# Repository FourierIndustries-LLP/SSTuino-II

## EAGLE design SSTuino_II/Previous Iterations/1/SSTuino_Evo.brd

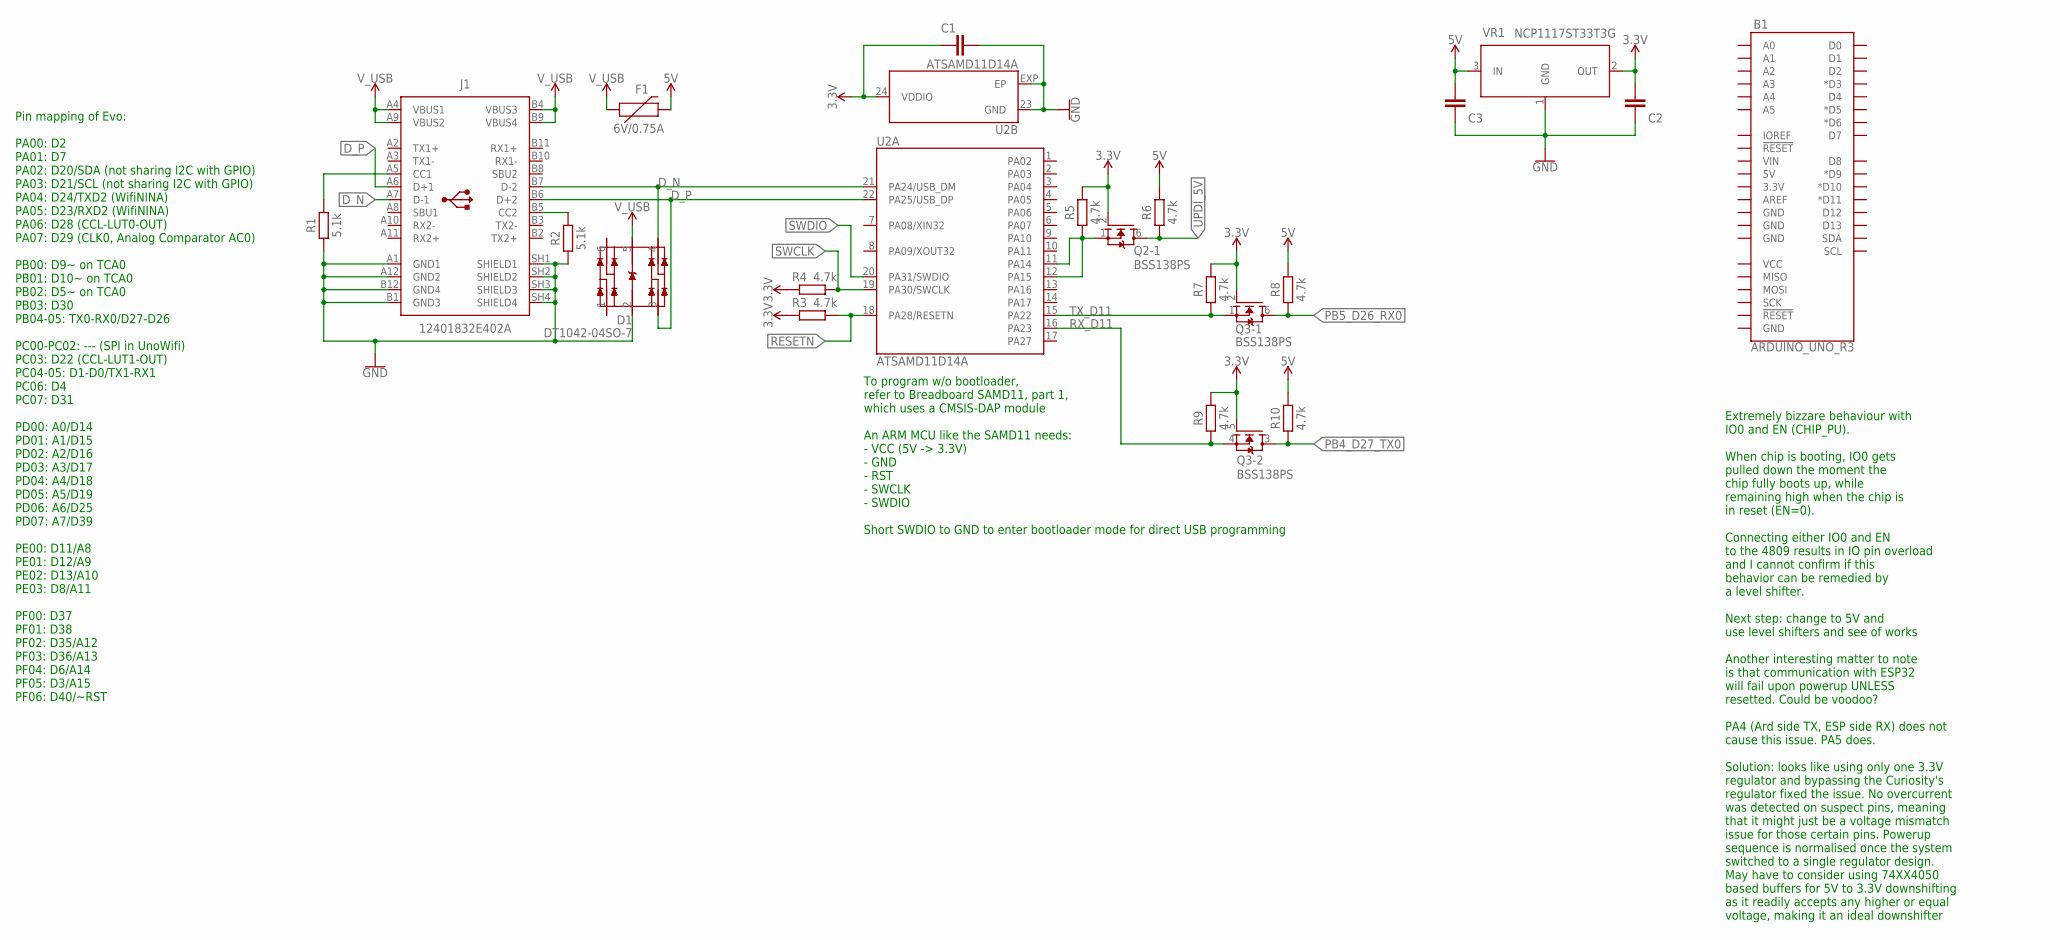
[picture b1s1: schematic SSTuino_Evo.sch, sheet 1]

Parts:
B1: ARDUINO_UNO_R3; ARDUINO_R3
C1: 100n; CAPC1005X60
C2, C3: 10uF; CAPC1608X85
D1: DT1042-04SO-7; SOT95P285X140-6N
F1: 6V/0.75A; 1206
J1: 12401832E402A
Q2, Q3: BSS138PS; ARDUINO-TRANSISTORS_SOT363
R1, R2: 5.1k; RESC1005X40
R3, R4, R5, R6, R7, R8, R9, R10: 4.7k; RESC1005X40
U2: ATSAMD11D14A; ARDUINO-UCS&SOCS_HVQFN24
VR1: NCP1117ST33T3G; SOT230P700X170-4

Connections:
3.3V: C1.1, C2.1, Q2.2 (G), Q3.2 (G), Q3.5 (G), R3.2, R4.2, R5.2, R7.2, R9.2, U2.24 (VDDIO), VR1.2 (OUT); also elsewhere on the board
5V: C3.1, F1.2, R6.2, R8.2, R10.2, VR1.3 (IN); also elsewhere on the board
CC1: J1.A5 (CC1), R1.2
CC2: J1.B5 (CC2), R2.2
D_N: D1.4 (IO3), J1.A7 (D-1), J1.B7 (D-2), U2.21 (PA24/USB_DM)
D_P: D1.3 (IO2), J1.A6 (D+1), J1.B6 (D+2), U2.22 (PA25/USB_DP)
GND: C1.2, C2.2, C3.2, D1.2 (VSS), J1.A1 (GND1), J1.A12 (GND2), J1.B1 (GND3), J1.B12 (GND4), J1.SH1 (SHIELD1), J1.SH2 (SHIELD2), J1.SH3 (SHIELD3), J1.SH4 (SHIELD4), R1.1, R2.1, U2.23 (GND), U2.EXP (EP), VR1.1 (GND); also elsewhere on the board
PB4_D27_TX0: Q3.3 (D), R10.1; also elsewhere on the board
PB5_D26_RX0: Q3.6 (D), R8.1; also elsewhere on the board
RESETN: R3.1, U2.18 (PA28/RESETN)
RX_D11: Q3.4 (S), R9.1, U2.16 (PA23)
SWCLK: R4.1, U2.19 (PA30/SWCLK)
SWDIO: U2.20 (PA31/SWDIO)
TX_D11: Q3.1 (S), R7.1, U2.15 (PA22)
UPDI_3V3: Q2.1 (S), R5.1, U2.11 (PA14), U2.12 (PA15)
UPDI_5V: Q2.6 (D), R6.1
V_USB: D1.5 (VCC), F1.1, J1.A4 (VBUS1), J1.A9 (VBUS2), J1.B4 (VBUS3), J1.B9 (VBUS4)

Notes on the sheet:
Pin mapping of Evo: PA00: D2 PA01: D7 PA02: D20/SDA (not sharing I2C with GPIO) PA03: D21/SCL (not sharing I2C with GPIO) PA04: D24/TXD2 (WifiNINA) PA05: D23/RXD2 (WifiNINA) PA06: D28 (CCL-LUT0-OUT) PA07: D29 (CLK0, Analog Comparator AC0) PB00: D9~ on TCA0 PB01: D10~ on TCA0 PB02: D5~ on TCA0 PB03: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
To program w/o bootloader, refer to Breadboard SAMD11, part 1, which uses a CMSIS-DAP module An ARM MCU like the SAMD11 needs: - VCC (5V -> 3.3V) - GND - RST - SWCLK - SWDIO Short SWDIO to GND to enter bootloader mode for direct USB programming
Extremely bizzare behaviour with IO0 and EN (CHIP_PU). When chip is booting, IO0 gets pulled down the moment the chip fully boots up, while remaining high when the chip is in reset (EN=0). Connecting either IO0 and EN to the 4809 results in IO pin overload and I cannot confirm if this behavior can 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

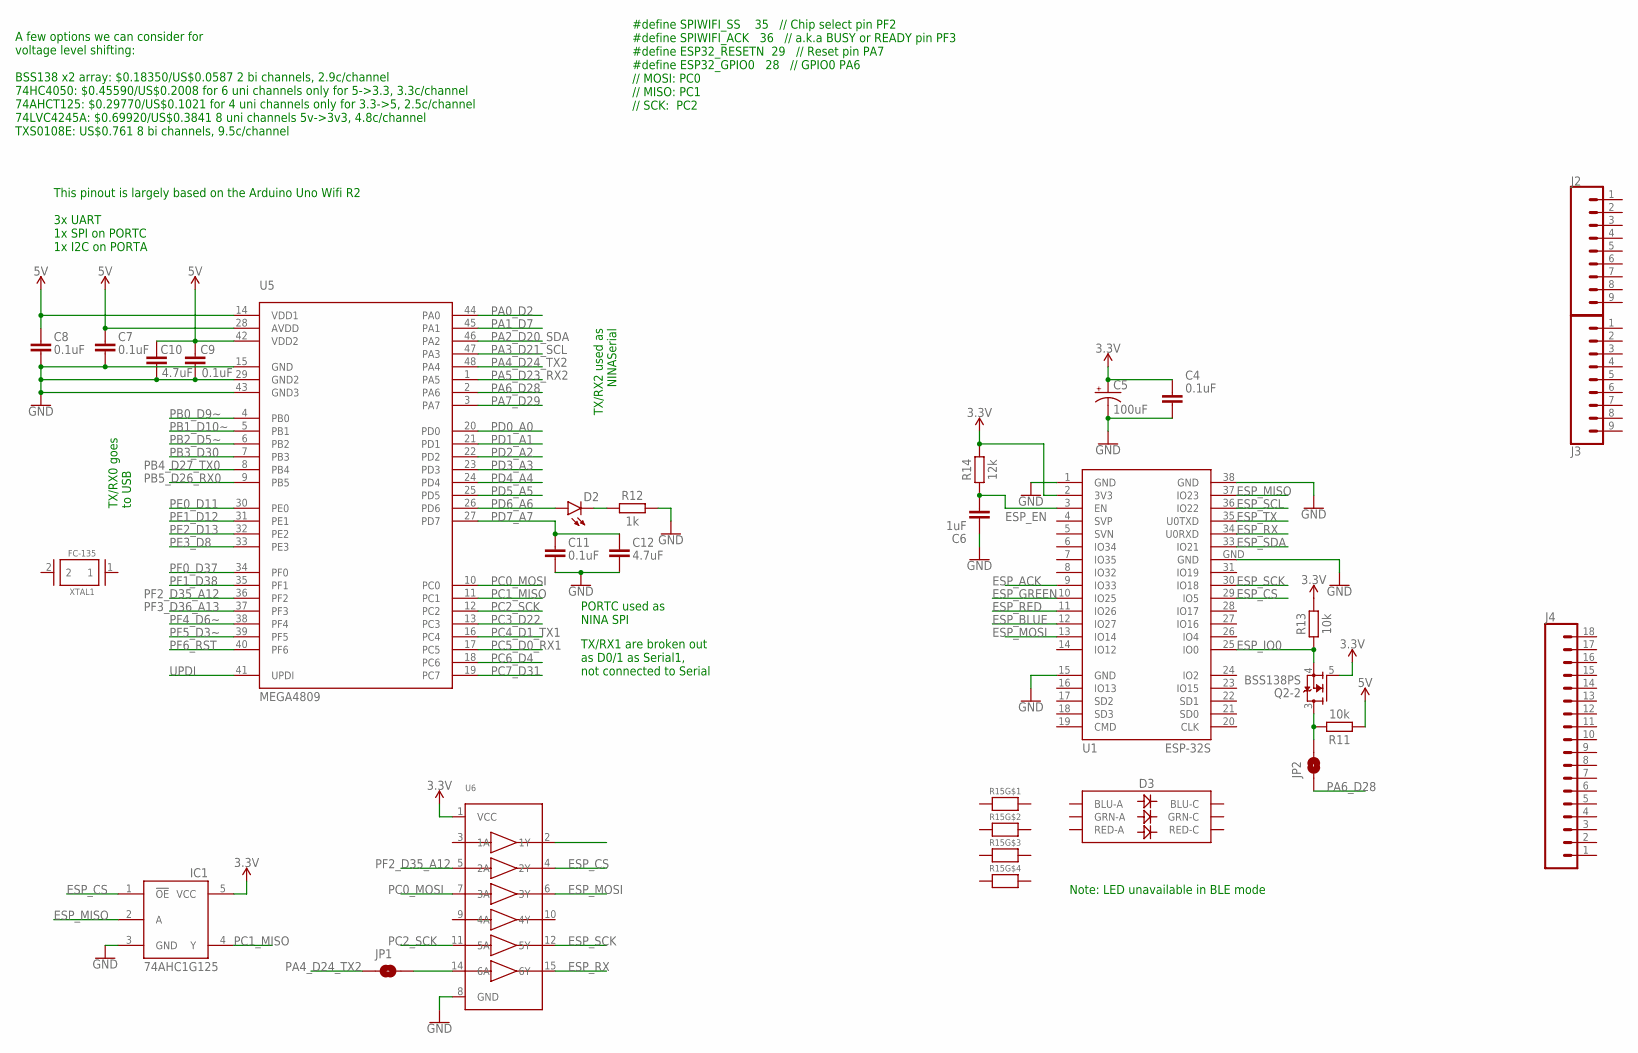
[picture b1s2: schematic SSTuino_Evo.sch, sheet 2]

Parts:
C4, C7, C8, C9, C11: 0.1uF; CAPC1005X60
C5: 100uF; CAPMP3216X180N
C6: 1uF; CAPC1005X60
C10, C12: 4.7uF; CAPC1005X60
D2: LED0603; LED-0603
D3: LED-RGBNO_IC; LED-TRICOLOR-5050
IC1: 74AHC1G125; SOT23-5L
J2, J3: CONN_09NO_SILK; 1X09_NO_SILK
J4: CONN_18; 1X18
JP1, JP2: JUMPER-SMT_2_NO_SILK; SMT-JUMPER_2_NO_SILK
Q2: BSS138PS; ARDUINO-TRANSISTORS_SOT363
R11, R13: 10k; RESC1005X40
R12: 1k; RESC1005X40
R14: 12k; RESC1005X40
R15: RESISTOR_4PACK; RESPACK_4X0603
U1: ESP-32S
U5: MEGA4809; TQFP48
U6: 74HC4050DTSSOP; TSSOP16
XTAL1: FC-135; XTAL330X1051X90N

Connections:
3.3V: C4.1, C5.1 (+), IC1.5 (VCC), Q2.5 (G), R13.2, R14.2, U1.2 (3V3), U6.1 (VCC); also elsewhere on the board
5V: C7.1, C8.1, C9.1, C10.1, R11.1, U5.14 (VDD1), U5.28 (AVDD), U5.42 (VDD2); also elsewhere on the board
ESP_ACK: U1.9 (IO33)
ESP_BLUE: U1.12 (IO27)
ESP_CS: IC1.1 (!OE), U1.29 (IO5), U6.4 (2Y)
ESP_EN: C6.2, R14.1, U1.3 (EN)
ESP_GREEN: U1.10 (IO25)
ESP_IO0: Q2.4 (S), R13.1, U1.25 (IO0)
ESP_MISO: IC1.2 (A), U1.37 (IO23)
ESP_MOSI: U1.13 (IO14), U6.6 (3Y)
ESP_RED: U1.11 (IO26)
ESP_RX: U1.34 (U0RXD), U6.15 (6Y)
ESP_SCK: U1.30 (IO18), U6.12 (5Y)
ESP_SCL: U1.36 (IO22)
ESP_SDA: U1.33 (IO21)
ESP_TX: U1.35 (U0TXD)
GND: C4.2, C5.2 (-), C6.1, C7.2, C8.2, C9.2, C10.2, C11.2, C12.2, IC1.3 (GND), R12.2, U1.1 (GND), U1.15 (GND), U1.38 (GND), U1.GND, U5.15 (GND), U5.29 (GND2), U5.43 (GND3), U6.8 (GND); also elsewhere on the board
unnamed: JP2.2, Q2.3 (D), R11.2
unnamed: D2.C, R12.1
unnamed: JP1.2, U6.14 (6A)
PA0_D2: U5.44 (PA0)
PA1_D7: U5.45 (PA1)
PA2_D20_SDA: U5.46 (PA2)
PA3_D21_SCL: U5.47 (PA3)
PA4_D24_TX2: JP1.1, U5.48 (PA4)
PA5_D23_RX2: U5.1 (PA5)
PA6_D28: JP2.1, U5.2 (PA6)
PA7_D29: U5.3 (PA7)
PB0_D9~: U5.4 (PB0)
PB1_D10~: U5.5 (PB1)
PB2_D5~: U5.6 (PB2)
PB3_D30: U5.7 (PB3)
PB4_D27_TX0: U5.8 (PB4); also elsewhere on the board
PB5_D26_RX0: U5.9 (PB5); also elsewhere on the board
PC0_MOSI: U5.10 (PC0), U6.7 (3A)
PC1_MISO: IC1.4 (Y), U5.11 (PC1)
PC2_SCK: U5.12 (PC2), U6.11 (5A)
PC3_D22: U5.13 (PC3)
PC4_D1_TX1: U5.16 (PC4)
PC5_D0_RX1: U5.17 (PC5)
PC6_D4: U5.18 (PC6)
PC7_D31: U5.19 (PC7)
PD0_A0: U5.20 (PD0)
PD1_A1: U5.21 (PD1)
PD2_A2: U5.22 (PD2)
PD3_A3: U5.23 (PD3)
PD4_A4: U5.24 (PD4)
PD5_A5: U5.25 (PD5)
PD6_A6: D2.A, U5.26 (PD6)
PD7_A7: C11.1, C12.1, U5.27 (PD7)
PE0_D11: U5.30 (PE0)
PE1_D12: U5.31 (PE1)
PE2_D13: U5.32 (PE2)
PE3_D8: U5.33 (PE3)
PF0_D37: U5.34 (PF0)
PF1_D38: U5.35 (PF1)
PF2_D35_A12: U5.36 (PF2), U6.5 (2A)
PF3_D36_A13: U5.37 (PF3)
PF4_D6~: U5.38 (PF4)
PF5_D3~: U5.39 (PF5)
PF6_RST: U5.40 (PF6)
UPDI: U5.41 (UPDI)

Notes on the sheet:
A few options we can consider for voltage level shifting: BSS138 x2 array: $0.18350/US$0.0587 2 bi channels, 2.9c/channel 74HC4050: $0.45590/US$0.2008 for 6 uni channels only for 5->3.3, 3.3c/channel 74AHCT125: $0.29770/US$0.1021 for 4 uni channels only for 3.3->5, 2.5c/channel 74LVC4245A: $0.69920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
This pinout is largely based on the Arduino Uno Wifi R2 3x UART 1x SPI on PORTC 1x I2C on PORTA
TX/RX2 used as NINASerial
PORTC used as NINA SPI
TX/RX1 are broken out as D0/1 as Serial1, not connected to Serial
TX/RX0 goes to USB
#define SPIWIFI_SS 35 // Chip select pin PF2 #define SPIWIFI_ACK 36 // a.k.a BUSY or READY pin PF3 #define ESP32_RESETN 29 // Reset pin PA7 #define ESP32_GPIO0 28 // GPIO0 PA6 // MOSI: PC0 // MISO: PC1 // SCK: PC2
Note: LED unavailable in BLE mode

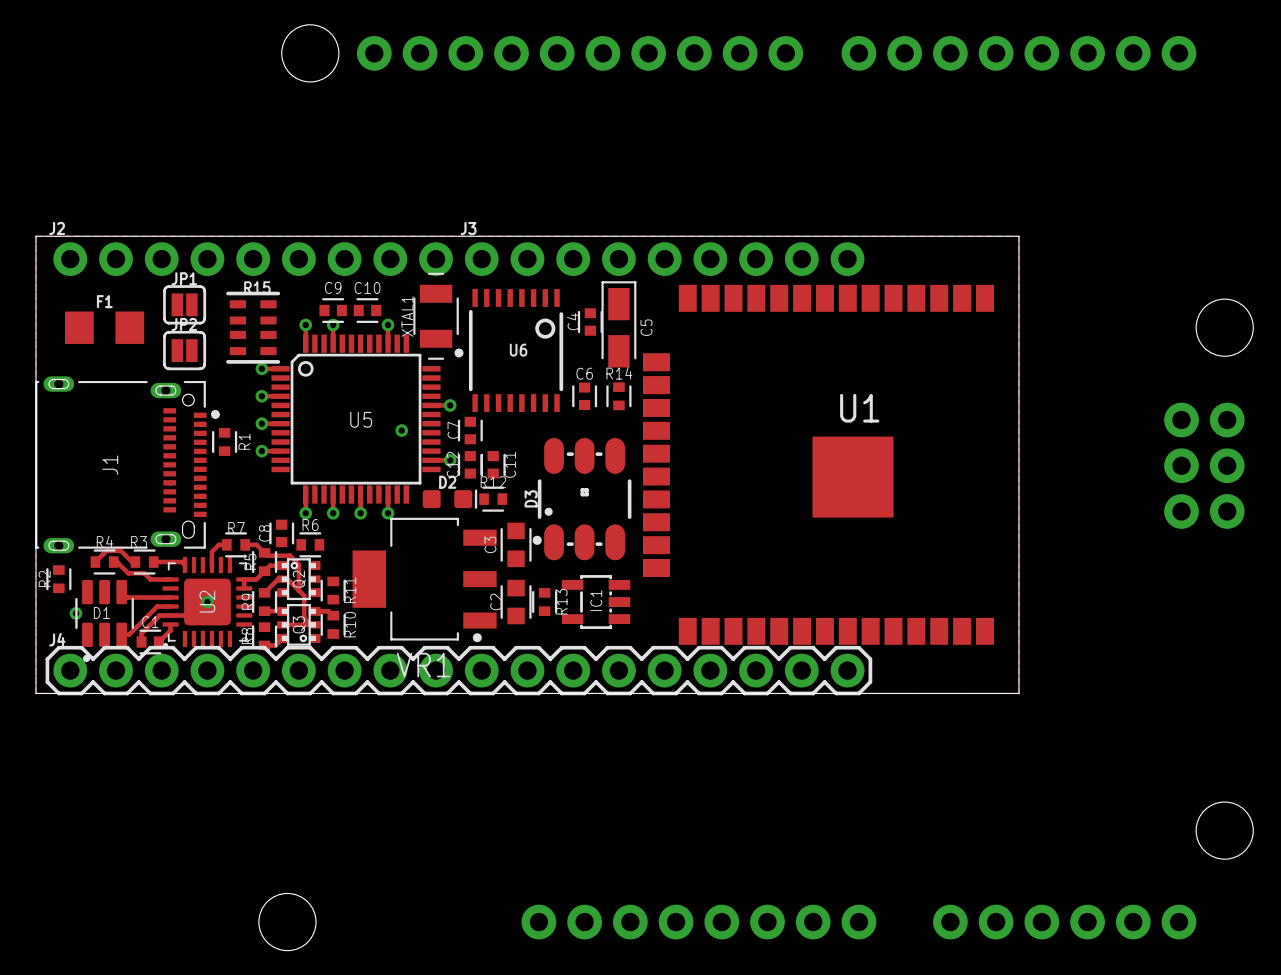
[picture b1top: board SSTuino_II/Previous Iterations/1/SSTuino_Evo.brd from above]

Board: 2 copper layers, 54.6 x 25.4 mm, 47 parts (0 on the bottom side), 34 nets.

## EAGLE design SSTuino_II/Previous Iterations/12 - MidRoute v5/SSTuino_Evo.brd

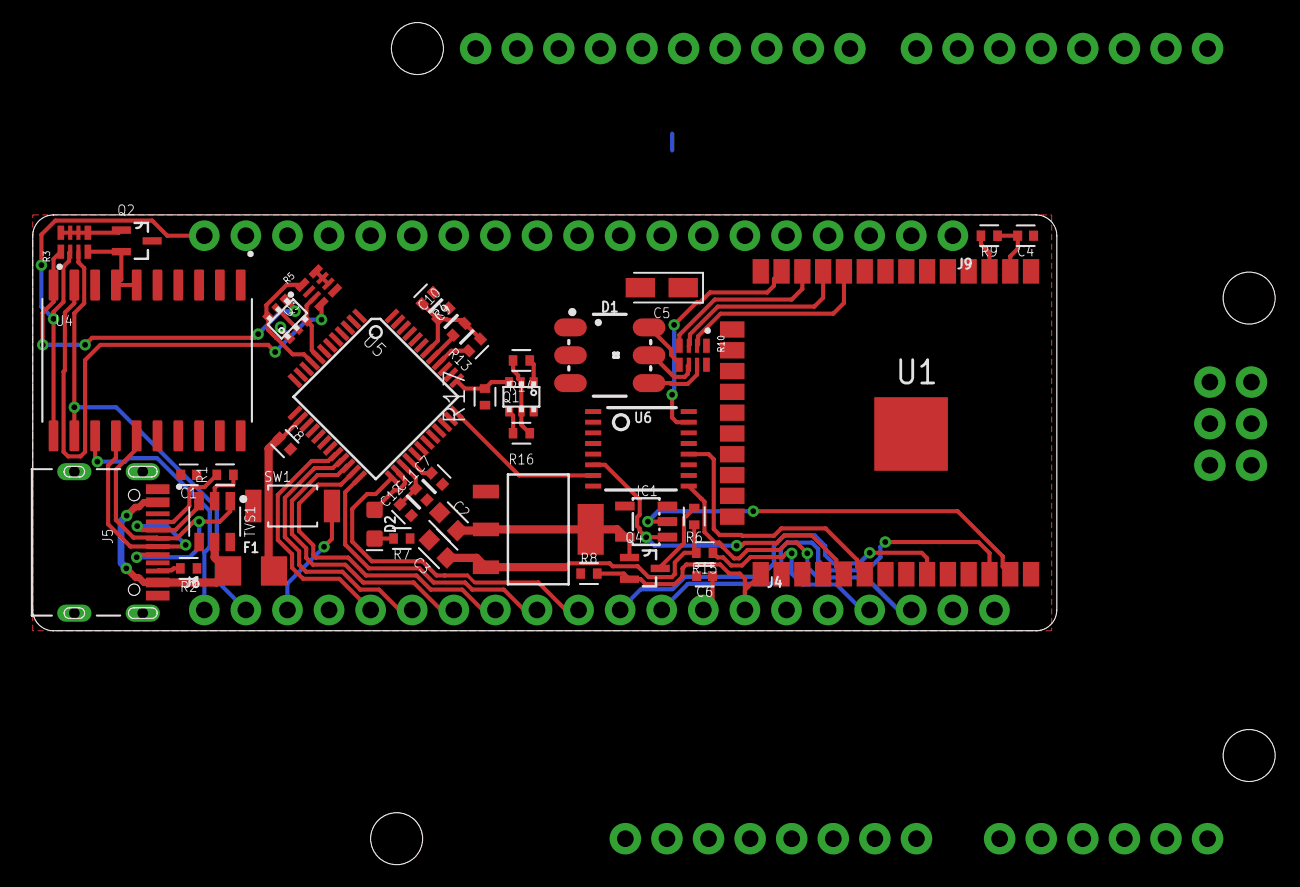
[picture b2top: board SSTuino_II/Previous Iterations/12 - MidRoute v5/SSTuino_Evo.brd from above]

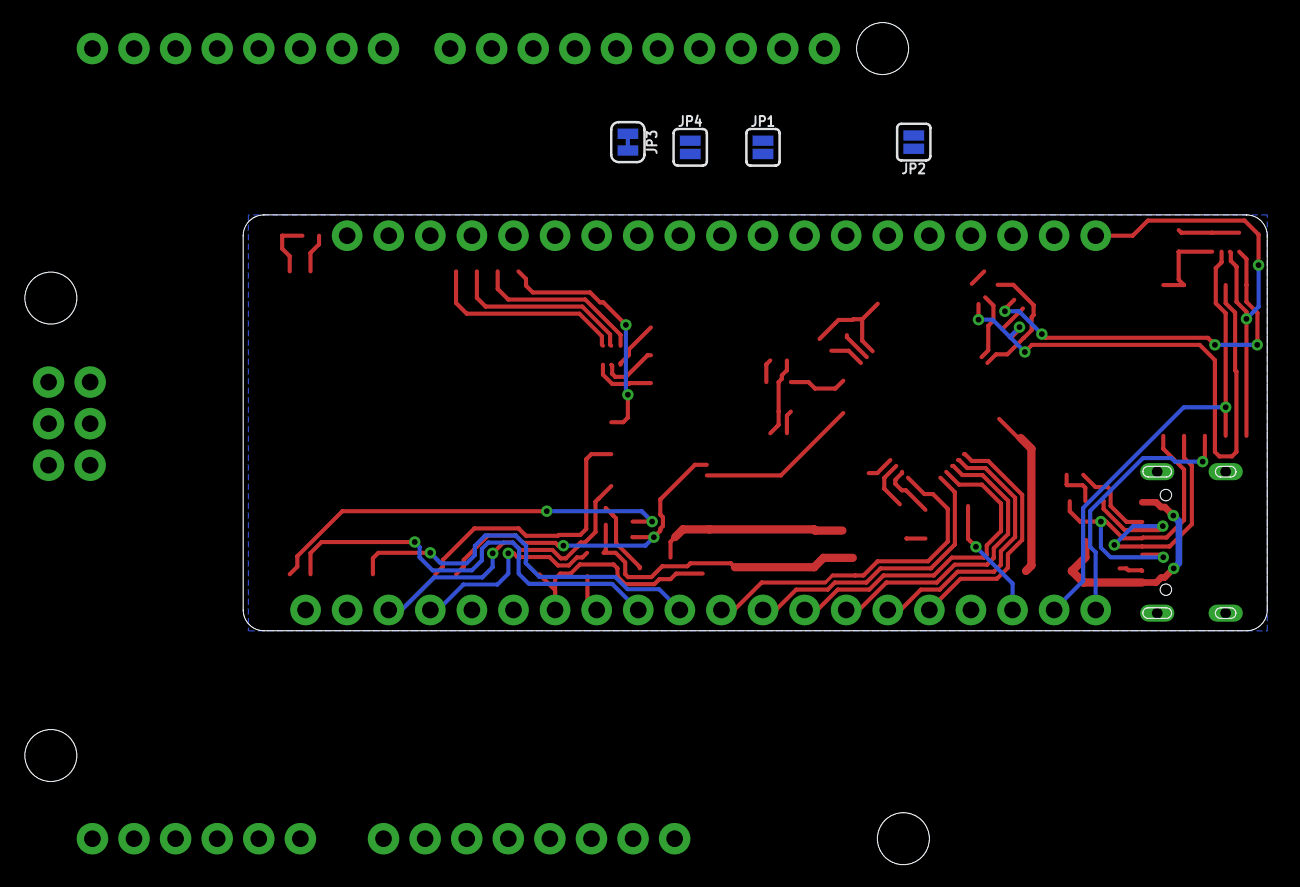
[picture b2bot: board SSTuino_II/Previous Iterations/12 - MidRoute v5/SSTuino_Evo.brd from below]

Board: 2 copper layers, 62.5 x 25.4 mm, 51 parts (4 on the bottom side), 73 nets.

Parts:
B1: ARDUINO_UNO_R3; ARDUINO_R3
C1: 100n; CAPC1005X60
C2, C3: 10uF; CAPC1608X85
C4, C7, C8, C9, C11: 0.1uF; CAPC1005X60
C5: 100uF; CAPMP3216X180N
C6: 1uF; CAPC1005X60
C10, C12: 4.7uF; CAPC1005X60
D1: LED-TRICOLOR-5050
D2: LED-0603
F1: 6V/0.75A; 1206
IC1: 74AHC1G125; SOT23-5L
J4: 1X06_NO_SILK
J5: TYPE-C-31-M-12; HRO_TYPE-C-31-M-12
J6: 1X14_NO_SILK
J9: 1X19_NO_SILK
JP1, JP2, JP4: SMT-JUMPER_2_NO_SILK
JP3: JUMPER-SMT_2_NC_TRACE_SILK; SMT-JUMPER_2_NC_TRACE_SILK
Q1, Q3: BSS138PS; ARDUINO-TRANSISTORS_SOT363
Q2, Q4: BSS138PW; SOT65P210X110-3N
R1, R2: 5.1k; RESC1005X40
R3, R5: 4.7k; RESPACK_4X0402
R4, R14, R15, R16, R17: 4.7k; RESC1005X40
R6, R8: 10k; RESC1005X40
R7: 1k; RESC1005X40
R9: 12k; RESC1005X40
R10: RESPACK_4X0402
R13: 100k; RESC1005X40
SW1: SKRKAEE020; SW2-2.6-3.9X2.9X1.5+0.4MM
TVS1: TPUSBLC6-2SC6; SOT95P280X110-6N
U1: ESP-32S
U3: AMS1117-3.3; SOT230P696X180-4N
U4: ATSAMD11D14A-SSNT; SOIC127P1030X265-20N
U5: MEGA4809; TQFP48
U6: TSSOP16

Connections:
3.3V: C1.1, C2.1, C4.1, C5.1, IC1.5, J6.4, Q1.2, Q1.5, Q2.1, Q3.2, Q3.5, Q4.1, R3.5, R3.6, R3.7, R3.8, R5.5, R8.2, R9.2, R14.2, R16.1, U1.2, U3.2, U3.4, U4.17, U6.1
5V: C3.1, C7.1, C8.1, C9.1, C10.1, F1.2, J4.6, R4.2, R5.6, R5.7, R5.8, R6.1, R13.2, R15.2, R17.1, U3.3, U5.14, U5.28, U5.42
BLU: D1.6, R10.5
CC1: J5.A5, R1.1
CC2: J5.B5, R2.2
D_N: J5.A7, J5.B7, TVS1.3, U4.14
D_P: J5.A6, J5.B6, TVS1.1, U4.15
ESP_ACK: Q1.4, R16.2, U1.9
ESP_BLUE: R10.4, U1.12
ESP_CS: IC1.1, U1.29, U6.6
ESP_EN: C6.2, J6.13, JP3.2, R9.1, U1.3
ESP_GREEN: R10.2, U1.10
ESP_IO0: J6.14, Q4.2, R8.1, U1.25
ESP_MISO: IC1.2, U1.37
ESP_MOSI: U1.13, U6.15
ESP_RED: R10.3, U1.11
ESP_RX: U1.34, U6.10
ESP_RX_5V: J4.4, JP1.2, U6.9
ESP_SCK: U1.30, U6.12
ESP_SCL: J6.12, U1.36
ESP_SDA: J6.11, U1.33
ESP_TX: Q1.1, R14.1, U1.35
ESP_TX_5V: J4.3, JP4.2, Q1.6, R15.1
GND: C1.2, C2.2, C3.2, C4.2, C5.2, C6.1, C7.2, C8.2, C9.2, C10.2, C11.2, C12.2, D1.1, D1.2, D1.3, IC1.3, J4.5, J5.A1B12, J5.B1A12, J5.S1, J5.S2, J5.S3, J5.S4, J9.15, R1.2, R2.1, R7.2, SW1.1, TVS1.2, U1.1, U1.15, U1.38, U1.GND, U3.1, U4.16, U5.15, U5.29, U5.43, U6.8
GRN: D1.4, R10.7
IO0_5V: JP2.2, Q4.3, R6.2
unnamed: D2.C, R7.1
unnamed: JP3.1, U6.2
PA0_D2: J9.3, U5.44
PA1_D7: J9.8, U5.45
PA2_D20_SDA: J9.17, U5.46
PA3_D21_SCL: J9.18, U5.47
PA4_D24_TX2: JP1.1, U5.48
PA5_D23_RX2: JP4.1, U5.1
PA6_D28: JP2.1, U5.2
PA7_D29: U5.3, U6.3
PB0_D9~: J9.10, U5.4
PB1_D10~: J9.11, U5.5
PB2_D5~: J9.6, U5.6
PB4_D27_TX0: Q3.3, R5.3, U5.8
PB5_D26_RX0: Q3.6, R5.1, U5.9
PC0_MOSI: U5.10, U6.14
PC1_MISO: IC1.4, U5.11
PC2_SCK: U5.12, U6.11
PC4_D1_TX1: J9.2, U5.16
PC5_D0_RX1: J9.1, U5.17
PC6_D4: J9.5, U5.18
PD0_A0: J6.5, U5.20
PD1_A1: J6.6, U5.21
PD2_A2: J6.7, U5.22
PD3_A3: J6.8, U5.23
PD4_A4: J6.9, U5.24
PD5_A5: J6.10, U5.25
PD6_A6: D2.A, U5.26
PD7_A7_AREF: C11.1, C12.1, J9.16, U5.27
PE0_D11: J9.12, U5.30
PE1_D12: J9.13, U5.31
PE2_D13: J9.14, U5.32
PE3_D8: J9.9, U5.33
PF2_D35_A12: U5.36, U6.7
PF3_D36_A13: Q1.3, R17.2, U5.37
PF4_D6~: J9.7, U5.38
PF5_D3~: J9.4, U5.39
PF6_RST: J6.3, R13.1, SW1.2, U5.40
RED: D1.5, R10.6
RESETN: J9.19, R3.2, U4.11
RX_D11: Q3.4, R3.1, U4.10
SWCLK: J6.2, R3.3, U4.12
SWDIO: J6.1, U4.13
TX_D11: Q3.1, R5.4, U4.9
UPDI: Q2.2, R3.4, U4.6, U4.7
UPDI_5V: Q2.3, R4.1, U5.41
V_USB: F1.1, J5.A4B9, J5.B4A9, TVS1.5

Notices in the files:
parts and their libraries:
esp32: Creative Commons Attribution-ShareAlike 4.0 International
SparkFun-Boards: Licensing: Creative Commons ShareAlike 4.0 International - https://creativecommons.org/licenses/by-sa/4.0
